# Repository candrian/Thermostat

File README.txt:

In the need of my new homemade energy saving fireplace (which boils water for the radiator) i designed and built a digital thermostat. The idea to design my own thermostat came when i came across with the following problem.
When i first fire the fireplace the water in the boiler around the fireplace is cool. After a few minutes the fireplace warms the water enough so that the water temp exceeds the thermostat limit. The thermostat changes state and drives an electric valve to move the water from the fireplace boiler to the radiators. The electric valve is slow enough and takes a few minutes to make a full turn. While the water is moving from the fireplace boiler to the radiators, circularly cool water is coming back in the fireplace boiler from the radiators. Τhe water temp in the fireplace boiler is getting cooler and after a few minutes falls under thermostat's limit. The thermostat changes state and stops the valve from driving the water to radiators. This happens again and again until the whole amount of water in the radiators is get warm. 
To prevent this problem from opening and closing the electric valve in so small time spaces i designed a thermostat that can delay the sample points. It check's the fireplace boiler temp and drives the electric valve once the water temp exceeds the thermostat limit. After that it waits for a half hour or more and then checks the water temp again.

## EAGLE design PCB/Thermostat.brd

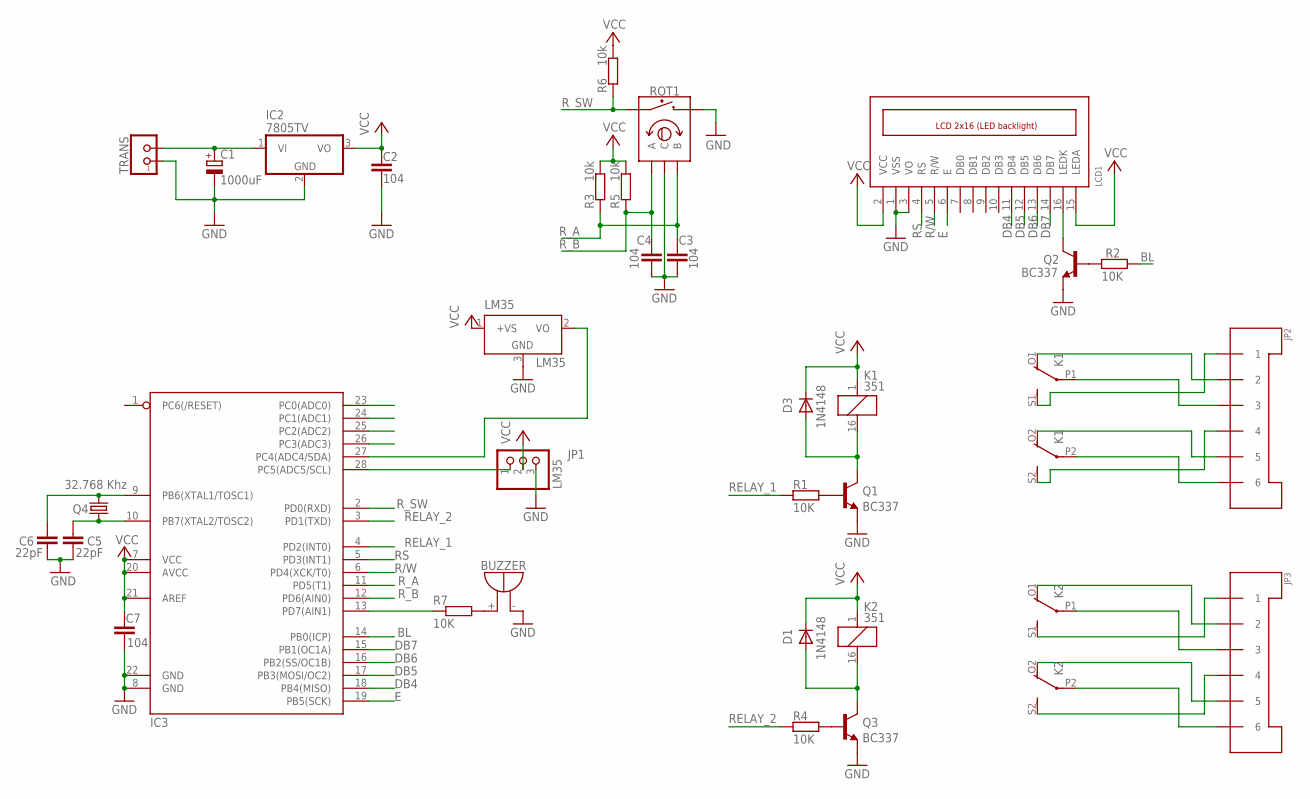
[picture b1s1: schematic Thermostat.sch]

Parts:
BUZZER: F/HMB
C1: 1000uF; C-TT2D13-SIDE
C2, C3, C4, C7: 104; C-22X6(FAKI)
C5, C6: 22pF; C-22X6(FAKI)
D1, D3: 1N4148; DO35-10
IC2: 7805TV; TO220V
IC3: ATMEGA-8-P; DIL28-3
JP1: LM35; 1X03
JP2, JP3: KLEMES_DELMAC_6
K1, K2: 351
LCD1: LCD-HD44780PINHEAD; HD44780-2X16-PINHEAD
LM35: LM35; TO-92
Q1, Q2, Q3: BC337; TO92-EBC
Q4: 32.768 Khz; TC38
R1, R2, R4, R7: 10K; R0270/10
R3, R5, R6: 10k; R0270/10
ROT1: ROTARY/5-PIN; 5-PIN/RP
TRANS: KLEMESX2

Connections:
BL: IC3.14 (PB0(ICP)), R2.2
DB4: IC3.18 (PB4(MISO)), LCD1.11 (DB4)
DB5: IC3.17 (PB3(MOSI/OC2)), LCD1.12 (DB5)
DB6: IC3.16 (PB2(SS/OC1B)), LCD1.13 (DB6)
DB7: IC3.15 (PB1(OC1A)), LCD1.14 (DB7)
E: IC3.19 (PB5(SCK)), LCD1.6 (E)
GND: BUZZER.-, C1.-, C2.2, C3.2, C4.2, C5.2, C6.2, C7.2, IC2.2 (GND), IC3.8 (GND), IC3.22 (GND), JP1.3, LCD1.1 (VSS), LCD1.3 (VO), LM35.3 (GND1), Q1.E, Q2.E, Q3.E, ROT1.C, ROT1.SW2, TRANS.1
unnamed: JP2.P$3 (3), K1.P1
unnamed: JP3.P$2 (2), K2.O1 (O)
unnamed: C1.+, IC2.1 (VI), TRANS.2
unnamed: D1.A, K2.16 (2), Q3.C
unnamed: C5.1, IC3.10 (PB7(XTAL2/TOSC2)), Q4.1
unnamed: Q3.B, R4.2
unnamed: JP3.P$6 (6), K2.P2
unnamed: BUZZER.+, R7.2
unnamed: IC3.13 (PD7(AIN1)), R7.1
unnamed: IC3.28 (PC5(ADC5/SCL)), JP1.1
unnamed: LCD1.16 (LEDK), Q2.C
unnamed: C6.1, IC3.9 (PB6(XTAL1/TOSC1)), Q4.2
unnamed: Q2.B, R2.1
unnamed: D3.A, K1.16 (2), Q1.C
unnamed: Q1.B, R1.2
unnamed: JP2.P$6 (6), K1.P2
unnamed: JP2.P$1 (1), K1.S1 (S)
unnamed: JP2.P$5 (5), K1.O2 (O)
unnamed: JP2.P$4 (4), K1.S2 (S)
unnamed: JP2.P$2 (2), K1.O1 (O)
unnamed: JP3.P$1 (1), K2.S1 (S)
unnamed: JP3.P$3 (3), K2.P1
unnamed: JP3.P$5 (5), K2.O2 (O)
unnamed: JP3.P$4 (4), K2.S2 (S)
unnamed: IC3.27 (PC4(ADC4/SDA)), LM35.2 (VO)
R/W: IC3.6 (PD4(XCK/T0)), LCD1.5 (R/W)
RELAY_1: IC3.4 (PD2(INT0)), R1.1
RELAY_2: IC3.3 (PD1(TXD)), R4.1
RS: IC3.5 (PD3(INT1)), LCD1.4 (RS)
R_A: C3.1, IC3.11 (PD5(T1)), R3.1, ROT1.B
R_B: C4.1, IC3.12 (PD6(AIN0)), R5.1, ROT1.A
R_SW: IC3.2 (PD0(RXD)), R6.1, ROT1.SW1
VCC: C2.1, C7.1, D1.C, D3.C, IC2.3 (VO), IC3.7 (VCC), IC3.20 (AVCC), IC3.21 (AREF), JP1.2, K1.1, K2.1, LCD1.2 (VCC), LCD1.15 (LEDA), LM35.1 (+VS), R3.2, R5.2, R6.2

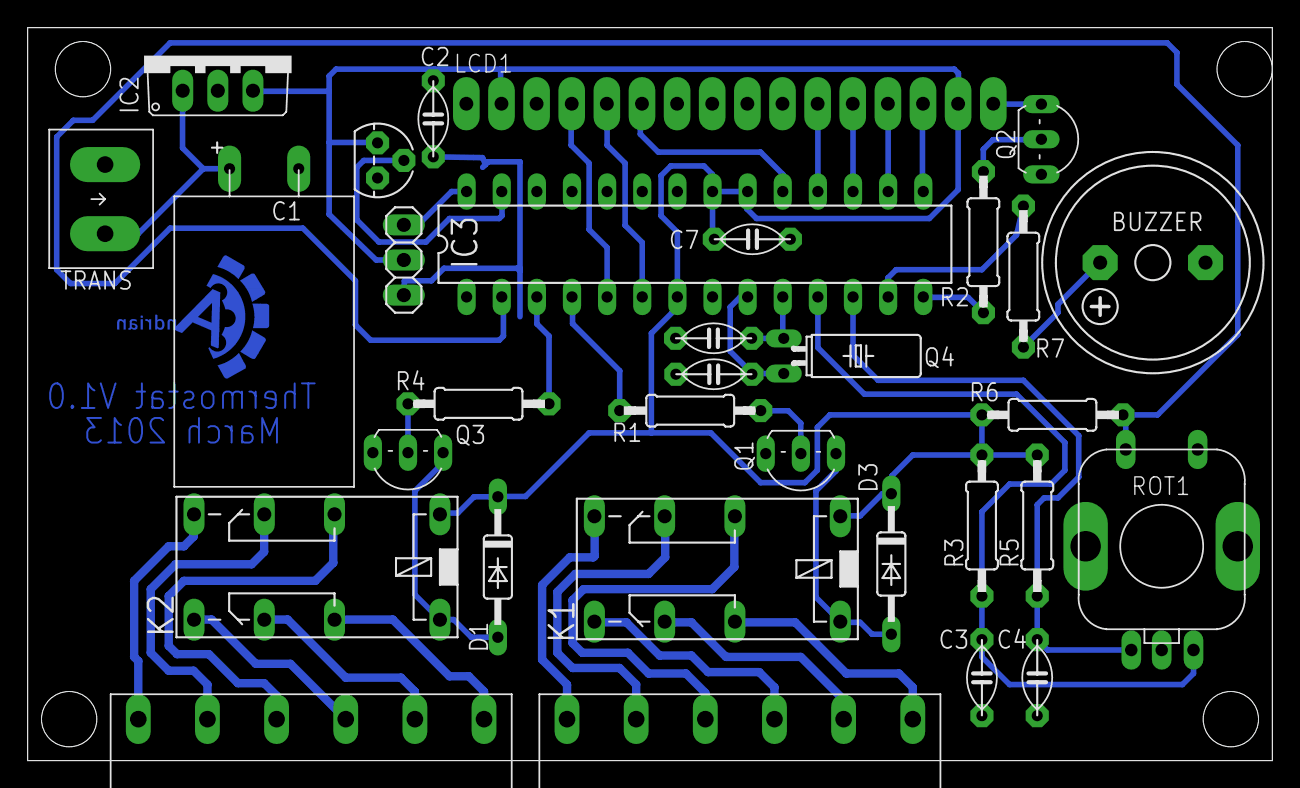
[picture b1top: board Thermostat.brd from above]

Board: 2 copper layers, 90.0 x 53.0 mm, 33 parts (0 on the bottom side), 40 nets.

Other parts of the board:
U$1: CANDRIAN-LOGO/SMALL/BOTTOM

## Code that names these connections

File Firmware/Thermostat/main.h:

#define BACKLIGHT       PB0
#define PORT_BACKLIGHT  PORTB
#define DDR_BACKLIGHT   DDRB


#define LM35_IN         PC4
#define LM35_PIPE       PC5
#define PORT_LM35       PORTC
#define DDR_LM35        DDRC

#define IN          0
#define PIPE        1

#define DEBOUNCE    0

#define R_A         PD5
#define R_B         PD6
#define R_SW        PD0

#define PORT_ROTARY PORTD
#define PIN_ROTARY  PIND
#define DDR_ROTARY  DDRD

#define PORT_BEEPER PORTD
#define DDR_BEEPER  DDRD
#define BEEPER      PD7

#define PORT_RELAY  PORTD
#define DDR_RELAY   DDRD
#define RELAY_1     PD2
#define RELAY_2     PD1

#define DEGREE      223 //Degree symbol

#define TIME        0
#define TEMP        1

#define NOTHING     0
#define RIGHT       1
#define LEFT        2
#define BUTTON      3
#define BUTTON_LONG 4

#define ON  0
#define OFF 1

#define IN_TEMP     2
#define PIPE_TEMP   3
#define SET_TIME    4

#define EE_IN_TEMP_1            0
#define EE_IN_TEMP_2            1
#define EE_PIPE_TEMP_1          2
#define EE_PIPE_TEMP_2          3
#define EE_SET_TIME_MINUTES_1   4
#define EE_SET_TIME_MINUTES_2   5
#define EE_SET_TIME_HOURS_1     6
#define EE_SET_TIME_HOURS_2     7

//Time struct
typedef struct{
	volatile uint8_t second; 
	volatile uint8_t minute;
	volatile uint8_t hour;
}time;
time t;
